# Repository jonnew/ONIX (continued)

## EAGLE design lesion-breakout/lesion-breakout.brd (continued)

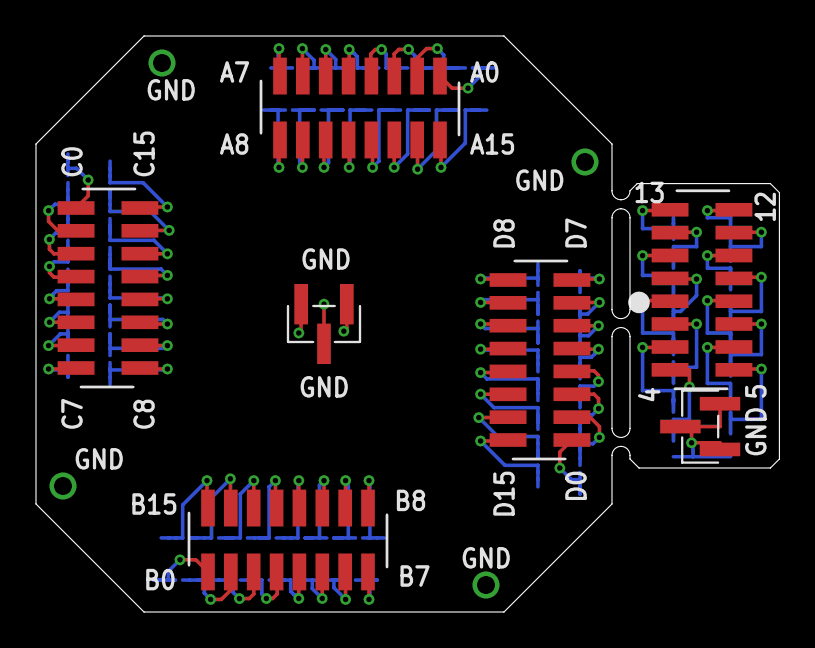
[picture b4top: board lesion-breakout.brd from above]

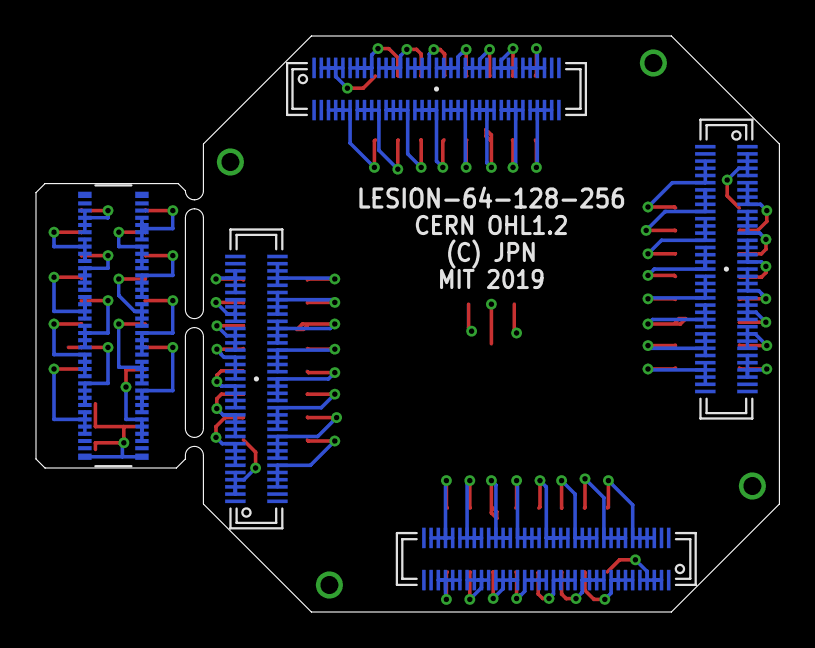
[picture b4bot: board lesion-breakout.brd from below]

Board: 2 copper layers, 41.3 x 32.0 mm, 16 parts (5 on the bottom side), 81 nets.

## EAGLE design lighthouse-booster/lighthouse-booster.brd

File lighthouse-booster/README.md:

# Lighthouse Synchronization Booster
This board is a modification for [HTC Vive Base
Stations](https://www.vive.com/us/accessory/base-station/) ("lighthouses") that
increases their range tracking range.

## Principle of Operation
HTC base stations work by producing alternating global synchronization flashes
using an IR LED array followed by laser curtain sweeps for 3D localization.
Because we use tiny photodiodes on our headstages (with about 1/10 the
effective area compared to those in the HTC headset), they are only capable of
working at ~3 meters from an unmodified base station. This issue is entirely
caused by the power of the global synchronization pulse. The synchronization
pulse must simultaneously blanket the entire room in IR light and therefore its
irradiance goes down as the square of distance from the base station.
Therefore, a very powerful LED array must be used. Conversely, because the
laser curtains are 2D sheets, their irradiance goes down linearly with distance
so they are easily received by the headstage at large distances without
modification.

This board is a drop in replacement for the standard LED array inside the HTC
Vive base station. It replaces the standard 15-LED array with an array of 120
LEDs.  Each set of 15 is controlled by a fast, low-side transistor switch. The
board draws about 700 mA DC at 12V. The pulse current (~60 us long, 2
MHz-modulated pulses operating at ~1% duty-cycle) is approximately 200A, with
5A for each LED.

## Power, Thermals, and Effective Tracking Distances
TODO

## Installation
TODO

## Gerber Files
{% include gerber_layers.md %}

## Bill of Materials
The BOM is located on [this google
sheet](https://docs.google.com/spreadsheets/d/1F-KWcdvH_63iXjZf0cgCfDiFX6XXW3qw6rlR8DZrFpQ/edit#gid=1349390549).

## License
Copyright Jonathan P. Newman 2017.

This documentation describes Open Hardware and is licensed under the
CERN OHL v.1.2.

You may redistribute and modify this documentation under the terms of the CERN
OHL v.1.2. (http://ohwr.org/cernohl). This documentation is distributed WITHOUT
ANY EXPRESS OR IMPLIED WARRANTY, INCLUDING OF MERCHANTABILITY, SATISFACTORY
QUALITY AND FITNESS FOR A PARTICULAR PURPOSE. Please see the CERN OHL v.1.2 for
applicable conditions

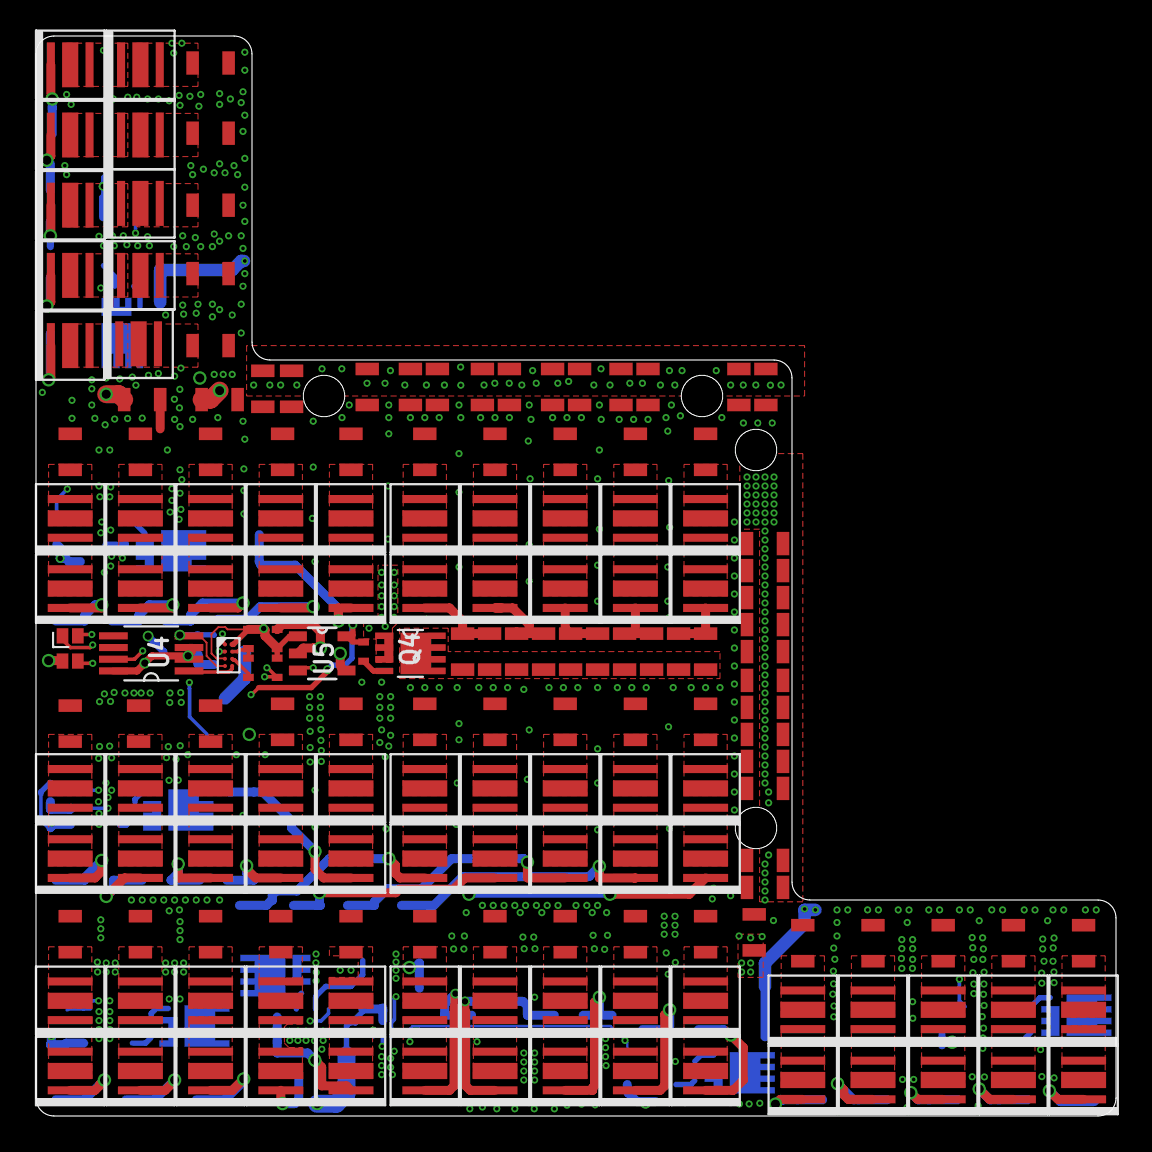
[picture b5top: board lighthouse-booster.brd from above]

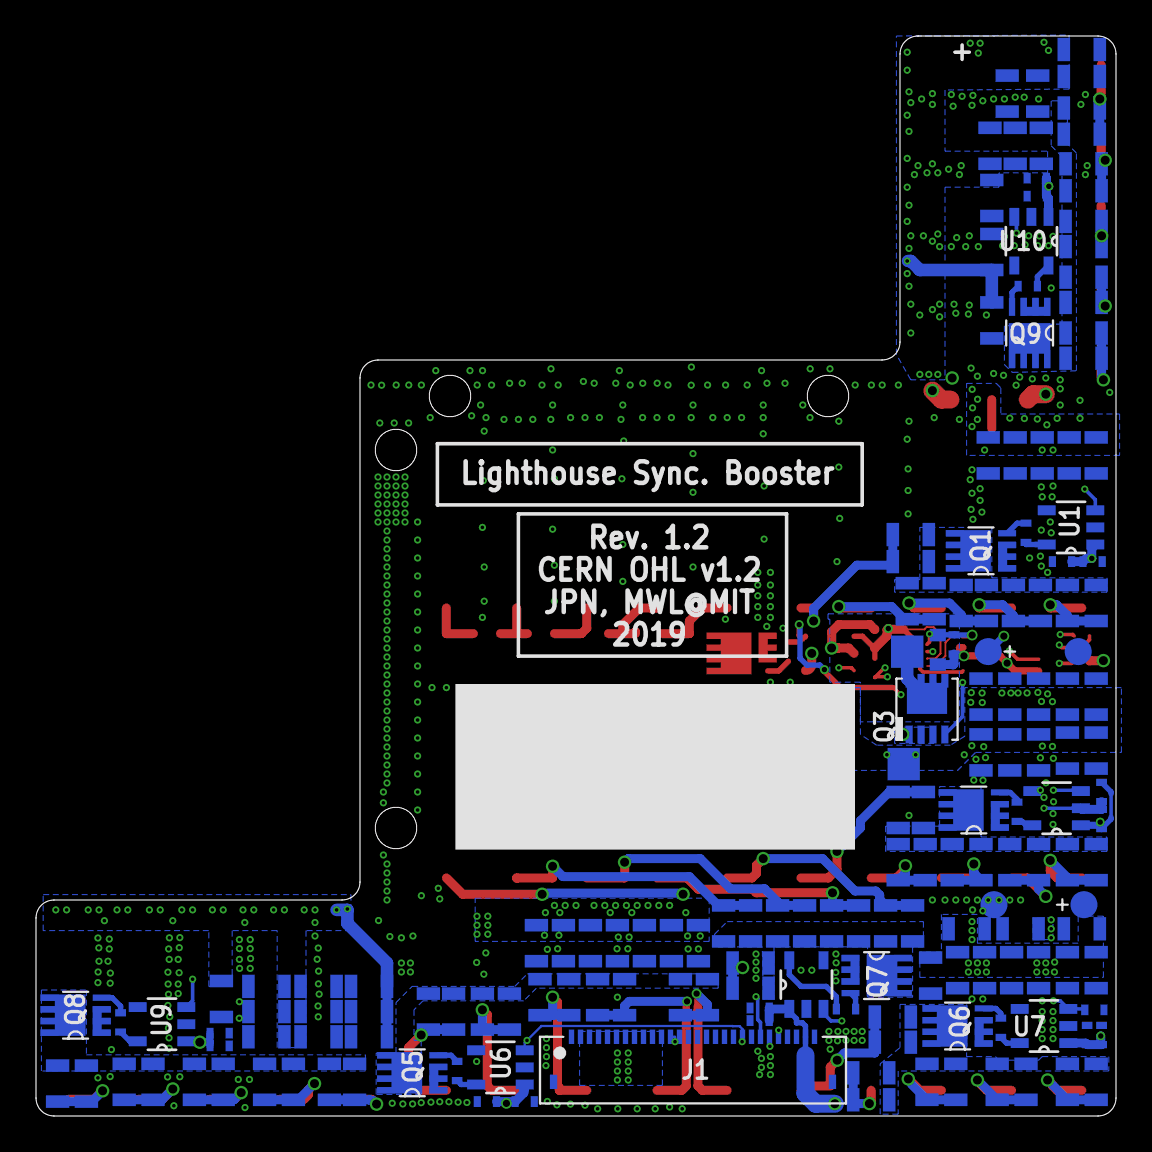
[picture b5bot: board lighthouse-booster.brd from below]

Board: 4 copper layers, 60.0 x 60.0 mm, 334 parts (166 on the bottom side), 157 nets.

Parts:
C1, C2, C6, C7, C11, C12, C13, C14, C16, C17, C18, C19, C20, C21, C22, C23, C24, C25, C26, C27, C30, C31, C32, C36, C37, C38, C42, C43, C44, C45, C46, C47, C48, C49, C50, C51, C52, C53, C54, C55, C56, C57, C58, C59, C60, C61, C62, C63, C64, C65, C66, C67, C68, C72, C73, C74, C78, C79, C80, C81, C82, C83, C84, C85, C86, C87, C88, C89, C90, C91, C92, C93, C94, C95, C96, C97, C98, C99, C100, C101: 22uF; 0805T
C3, C4, C10, C33, C34, C35, C69, C70, C71: 0.1uF; 0402T
C5: 4.7uF; 0603T
C8, C9, C39, C40, C41, C75, C76, C77: 10nF; 0402T
C15: 100pF; 0402T
C28, C29: 2.2mF; C5MMA-SMD
D2, D3, D5, D6, D8, D9, D11, D12, D14, D15, D17, D18, D20, D21, D23, D24, D26, D27, D29, D30, D33, D34, D36, D37, D39, D40, D42, D43, D45, D46, D48, D49, D51, D52, D54, D55, D57, D58, D60, D61, D63, D64, D66, D67, D69, D70, D72, D73, D75, D76, D78, D79, D81, D82, D84, D85, D87, D88, D90, D91, D93, D94, D96, D97, D99, D100, D102, D103, D105, D106, D108, D109, D111, D112, D114, D115, D117, D118, D120, D121: LUXEON-3.7MM
D31: LTST-C19HE1WT
J1: AYF532835; Y5B/Y5BW-28
L1, L2, L3, L4, L5, L6, L7, L8, L9, L10, L11, L12, L13, L14, L15, L16, L17, L18, L19, L20, L21, L22, L23, L24, L25, L26, L27, L28, L29, L30, L31, L32, L33, L34, L35, L36, L37, L38, L39, L40: 0805T
Q1, Q2, Q4, Q5, Q6, Q7, Q8, Q9: BSZ034N04LSATMA1; PG-TSDSON-8
Q3: Si7655ADN; POWERPACK-1212-8
R1, R2, R3, R4, R6, R7, R8, R9, R11, R12, R13, R14, R15, R16, R17, R18, R21, R22, R23, R24, R25, R26, R27, R28, R29, R30, R31, R32, R33, R34, R35, R36, R37, R38, R39, R40, R41, R42, R43, R44, R45, R46, R47, R48, R52, R53, R54, R55, R56, R57, R58, R59, R60, R61, R62, R63, R64, R65, R66, R67, R68, R69, R70, R71, R72, R73, R74, R75, R76, R77, R78, R79, R80, R81, R85, R86, R87, R88, R89, R90: 0.36; 0805T
R5, R10: 10k; 0402T
R19, R20, R49, R50, R51, R82, R83, R84: 10; 0402T
TP1, TP2: TP18SQ
U1, U2, U5, U6, U7, U8, U9, U10: UCC27517DBVR; SOT-23-5
U3: SN74LVC1G123YZPR; DSBGA8-1.9X0.9MM
U4: LTC1693-5; MSOP-8-3X3

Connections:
+5V0: C3.1, C4.1, C8.1, C9.1, C33.1, C34.1, C35.1, C39.1, C40.1, C41.1, C69.1, C70.1, C71.1, C75.1, C76.1, C77.1, D31.4, J1.27, R10.1, U1.1, U2.1, U3.A2, U3.C1, U5.1, U6.1, U7.1, U8.1, U9.1, U10.1
+12V: C1.2, C2.2, C6.2, C7.2, C11.2, C12.2, C13.2, C14.2, C16.2, C17.2, C18.1, C19.1, C20.1, C21.1, C22.1, C23.1, C24.1, C25.1, C26.1, C27.1, C28.A, C29.A, C30.2, C31.2, C32.2, C36.2, C37.2, C38.2, C42.2, C43.2, C44.2, C45.2, C46.2, C47.2, C48.2, C49.2, C50.2, C51.1, C52.1, C53.1, C54.1, C55.1, C56.1, C57.1, C58.1, C59.1, C60.1, C61.1, C62.1, C63.1, C64.1, C65.1, C66.2, C67.2, C68.2, C72.2, C73.2, C74.2, C78.2, C79.2, C80.2, C81.2, C82.2, C83.2, C84.2, C85.2, C86.1, C87.1, C88.1, C89.1, C90.1, C91.1, C92.1, C93.1, C94.1, C95.1, C96.1, C97.1, C98.1, C99.1, C100.1, C101.1, L1.1, L2.1, L3.1, L4.1, L5.1, L6.1, L7.1, L8.1, L9.1, L10.1, L11.1, L12.1, L13.1, L14.1, L15.1, L16.1, L17.1, L18.1, L19.1, L20.1, L21.1, L22.1, L23.1, L24.1, L25.1, L26.1, L27.1, L28.1, L29.1, L30.1, L31.1, L32.1, L33.1, L34.1, L35.1, L36.1, L37.1, L38.1, L39.1, L40.1, TP2.TP
BLUE_C: D31.3, J1.24
GND: C1.1, C2.1, C3.2, C4.2, C5.2, C6.1, C7.1, C8.2, C9.2, C10.2, C11.1, C12.1, C13.1, C14.1, C16.1, C17.1, C18.2, C19.2, C20.2, C21.2, C22.2, C23.2, C24.2, C25.2, C26.2, C27.2, C28.C, C29.C, C30.1, C31.1, C32.1, C33.2, C34.2, C35.2, C36.1, C37.1, C38.1, C39.2, C40.2, C41.2, C42.1, C43.1, C44.1, C45.1, C46.1, C47.1, C48.1, C49.1, C50.1, C51.2, C52.2, C53.2, C54.2, C55.2, C56.2, C57.2, C58.2, C59.2, C60.2, C61.2, C62.2, C63.2, C64.2, C65.2, C66.1, C67.1, C68.1, C69.2, C70.2, C71.2, C72.1, C73.1, C74.1, C75.2, C76.2, C77.2, C78.1, C79.1, C80.1, C81.1, C82.1, C83.1, C84.1, C85.1, C86.2, C87.2, C88.2, C89.2, C90.2, C91.2, C92.2, C93.2, C94.2, C95.2, C96.2, C97.2, C98.2, C99.2, C100.2, C101.2, J1.1, J1.12, J1.13, J1.14, J1.15, J1.19, J1.21, J1.25, J1.28, Q1.1, Q1.2, Q1.3, Q2.1, Q2.2, Q2.3, Q4.1, Q4.2, Q4.3, Q5.1, Q5.2, Q5.3, Q6.1, Q6.2, Q6.3, Q7.1, Q7.2, Q7.3, Q8.1, Q8.2, Q8.3, Q9.1, Q9.2, Q9.3, R5.1, U1.2, U1.4, U2.2, U2.4, U3.A1, U3.D1, U4.4, U5.2, U5.4, U6.2, U6.4, U7.2, U7.4, U8.2, U8.4, U9.2, U9.4, U10.2, U10.4
GREEN_C: D31.2, J1.23
unnamed: D76.C, R54.2, R57.2
unnamed: D75.C, D76.A1, D76.A2
unnamed: D75.A1, D75.A2, L35.2
unnamed: Q6.5, Q6.6, Q6.7, Q6.8, R27.1, R30.1, R33.1, R36.1, R39.1, R42.1, R45.1, R48.1, R54.1, R57.1
unnamed: R49.1, U7.5
unnamed: D58.C, R39.2, R42.2
unnamed: D57.C, D58.A1, D58.A2
unnamed: D67.C, R45.2, R48.2
unnamed: D66.C, D67.A1, D67.A2
unnamed: D66.A1, D66.A2, L34.2
unnamed: D30.C, R22.2, R24.2
unnamed: D57.A1, D57.A2, L33.2
unnamed: D49.C, R33.2, R36.2
unnamed: D48.C, D49.A1, D49.A2
unnamed: D48.A1, D48.A2, L32.2
unnamed: D40.C, R27.2, R30.2
unnamed: D39.C, D40.A1, D40.A2
unnamed: D39.A1, D39.A2, L31.2
unnamed: D29.C, D30.A1, D30.A2
unnamed: D29.A1, D29.A2, L20.2
unnamed: Q2.5, Q2.6, Q2.7, Q2.8, R2.1, R4.1, R7.1, R9.1, R12.1, R14.1, R16.1, R18.1, R22.1, R24.1
unnamed: R82.1, U8.5
unnamed: Q6.4, R49.2
unnamed: R50.1, U3.B1, U5.5
unnamed: Q1.4, R19.2
unnamed: R20.1, U2.5
unnamed: Q5.4, R51.2
unnamed: R83.1, U9.5
unnamed: D24.C, R16.2, R18.2
unnamed: D23.C, D24.A1, D24.A2
unnamed: D23.A1, D23.A2, L19.2
unnamed: D18.C, R12.2, R14.2
unnamed: D17.C, D18.A1, D18.A2
unnamed: D17.A1, D17.A2, L18.2
unnamed: D12.C, R7.2, R9.2
unnamed: D11.C, D12.A1, D12.A2
unnamed: D11.A1, D11.A2, L17.2
unnamed: D6.C, R2.2, R4.2
unnamed: D5.C, D6.A1, D6.A2
unnamed: D5.A1, D5.A2, L16.2
unnamed: Q2.4, R20.2
unnamed: R84.1, U10.5
unnamed: C15.1, R10.2, U3.B2
unnamed: U3.D2, U4.1
unnamed: C15.2, U3.C2
unnamed: C5.1, C10.1, J1.2, J1.3, J1.4, J1.5, J1.6, J1.7, J1.8, J1.9, J1.10, J1.11, Q3.1, Q3.2, Q3.3, U4.3, U4.8
unnamed: D27.C, R21.2, R23.2
unnamed: D26.C, D27.A1, D27.A2
unnamed: D26.A1, D26.A2, L5.2
unnamed: Q1.5, Q1.6, Q1.7, Q1.8, R1.1, R3.1, R6.1, R8.1, R11.1, R13.1, R15.1, R17.1, R21.1, R23.1
unnamed: Q3.5, Q3.6, Q3.7, Q3.8, Q3.PAD, TP1.TP
unnamed: D21.C, R15.2, R17.2
unnamed: D20.C, D21.A1, D21.A2
unnamed: D20.A1, D20.A2, L4.2
unnamed: D15.C, R11.2, R13.2
unnamed: D14.C, D15.A1, D15.A2
unnamed: D14.A1, D14.A2, L3.2
unnamed: D9.C, R6.2, R8.2
unnamed: D8.C, D9.A1, D9.A2
unnamed: D8.A1, D8.A2, L2.2
unnamed: D3.C, R1.2, R3.2
unnamed: D2.C, D3.A1, D3.A2
unnamed: D2.A1, D2.A2, L1.2
unnamed: R19.1, U1.5
unnamed: Q3.4, U4.7
unnamed: D70.C, R52.2, R55.2
unnamed: D69.C, D70.A1, D70.A2
unnamed: D69.A1, D69.A2, L10.2
unnamed: Q4.5, Q4.6, Q4.7, Q4.8, R25.1, R28.1, R31.1, R34.1, R37.1, R40.1, R43.1, R46.1, R52.1, R55.1
unnamed: D61.C, R43.2, R46.2
unnamed: D60.C, D61.A1, D61.A2
unnamed: D60.A1, D60.A2, L9.2
unnamed: D52.C, R37.2, R40.2
unnamed: D51.C, D52.A1, D52.A2
unnamed: D51.A1, D51.A2, L8.2
unnamed: D43.C, R31.2, R34.2
unnamed: D42.C, D43.A1, D43.A2
unnamed: D42.A1, D42.A2, L7.2
unnamed: D34.C, R25.2, R28.2
unnamed: D33.C, D34.A1, D34.A2
unnamed: D33.A1, D33.A2, L6.2
unnamed: Q4.4, R50.2
unnamed: D115.C, R85.2, R88.2
unnamed: D114.C, D115.A1, D115.A2
unnamed: D114.A1, D114.A2, L15.2
unnamed: Q7.5, Q7.6, Q7.7, Q7.8, R58.1, R61.1, R64.1, R67.1, R70.1, R73.1, R76.1, R79.1, R85.1, R88.1
unnamed: D106.C, R76.2, R79.2
unnamed: D105.C, D106.A1, D106.A2
unnamed: D105.A1, D105.A2, L14.2
unnamed: D97.C, R70.2, R73.2
unnamed: D96.C, D97.A1, D97.A2
unnamed: D96.A1, D96.A2, L13.2
unnamed: D88.C, R64.2, R67.2
unnamed: D87.C, D88.A1, D88.A2
unnamed: D87.A1, D87.A2, L12.2
unnamed: D79.C, R58.2, R61.2
unnamed: D78.C, D79.A1, D79.A2
unnamed: D78.A1, D78.A2, L11.2
unnamed: Q7.4, R82.2
unnamed: D73.C, R53.2, R56.2
unnamed: D72.C, D73.A1, D73.A2
unnamed: D72.A1, D72.A2, L25.2
unnamed: Q5.5, Q5.6, Q5.7, Q5.8, R26.1, R29.1, R32.1, R35.1, R38.1, R41.1, R44.1, R47.1, R53.1, R56.1
unnamed: D64.C, R44.2, R47.2
unnamed: D63.C, D64.A1, D64.A2
unnamed: D63.A1, D63.A2, L24.2
unnamed: D55.C, R38.2, R41.2
unnamed: D54.C, D55.A1, D55.A2
unnamed: D54.A1, D54.A2, L23.2
unnamed: D46.C, R32.2, R35.2
unnamed: D45.C, D46.A1, D46.A2
unnamed: D45.A1, D45.A2, L22.2
unnamed: D37.C, R26.2, R29.2
unnamed: D36.C, D37.A1, D37.A2
unnamed: D36.A1, D36.A2, L21.2
unnamed: R51.1, U6.5
unnamed: D118.C, R86.2, R89.2
unnamed: D117.C, D118.A1, D118.A2
unnamed: D117.A1, D117.A2, L30.2
unnamed: Q8.5, Q8.6, Q8.7, Q8.8, R59.1, R62.1, R65.1, R68.1, R71.1, R74.1, R77.1, R80.1, R86.1, R89.1
unnamed: D109.C, R77.2, R80.2
unnamed: D108.C, D109.A1, D109.A2
unnamed: D108.A1, D108.A2, L29.2
unnamed: D100.C, R71.2, R74.2
unnamed: D99.C, D100.A1, D100.A2
unnamed: D99.A1, D99.A2, L28.2
unnamed: D91.C, R65.2, R68.2
unnamed: D90.C, D91.A1, D91.A2
unnamed: D90.A1, D90.A2, L27.2
unnamed: D82.C, R59.2, R62.2
unnamed: D81.C, D82.A1, D82.A2
unnamed: D81.A1, D81.A2, L26.2
unnamed: Q8.4, R83.2
unnamed: D121.C, R87.2, R90.2
unnamed: D120.C, D121.A1, D121.A2
unnamed: D120.A1, D120.A2, L40.2
unnamed: Q9.5, Q9.6, Q9.7, Q9.8, R60.1, R63.1, R66.1, R69.1, R72.1, R75.1, R78.1, R81.1, R87.1, R90.1
unnamed: D112.C, R78.2, R81.2
unnamed: D111.C, D112.A1, D112.A2
unnamed: D111.A1, D111.A2, L39.2
unnamed: D103.C, R72.2, R75.2
unnamed: D102.C, D103.A1, D103.A2
unnamed: D102.A1, D102.A2, L38.2
unnamed: D94.C, R66.2, R69.2
unnamed: D93.C, D94.A1, D94.A2
unnamed: D93.A1, D93.A2, L37.2
unnamed: D85.C, R60.2, R63.2
unnamed: D84.C, D85.A1, D85.A2
unnamed: D84.A1, D84.A2, L36.2
unnamed: Q9.4, R84.2
RED_C: D31.1, J1.22
SYNC: J1.20, R5.2, U1.3, U2.3, U5.3, U6.3, U7.3, U8.3, U9.3, U10.3

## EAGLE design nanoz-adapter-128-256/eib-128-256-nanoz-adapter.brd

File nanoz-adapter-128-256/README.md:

# nanoz-adapter-128-256
Multiplexed adapter to interface eib-128 and eib-256 with the popular
[nanoZ](http://www.white-matter.com/nanoz/) electrode impedance tester and
plating device.

## Gerber Files
{% include gerber_layers.md %}

## Bill of Materials
The BOM is located on [this google
sheet](https://docs.google.com/spreadsheets/d/1F-KWcdvH_63iXjZf0cgCfDiFX6XXW3qw6rlR8DZrFpQ/edit#gid=889124438).

## Electrode Mapping
The NanoZ internal channel number to EIB mapping for [eib-128](../README.md) and [eib-256](../eib-256/README.md) are provided in the following google sheets:
- [eib-128 channel mapping](https://docs.google.com/spreadsheets/d/11wRDYOqHN5lPb03yUdfXfK0zvaDYsVetplaNK-R90Gg/edit#gid=663991061)
- [eib-256 channel mapping](https://docs.google.com/spreadsheets/d/11wRDYOqHN5lPb03yUdfXfK0zvaDYsVetplaNK-R90Gg/edit#gid=538743909)

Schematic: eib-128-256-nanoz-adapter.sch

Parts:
A: DF40HEAD; DF40-70REC
B: DF40HEAD; DF40-70REC
C: DF40HEAD; DF40-70REC
C1, C2, C5, C6, C10, C12, C13, C15, C20, C22, C23, C25, C29, C30, C33, C34: 1uF; 0603
C3, C4, C7, C8, C9, C11, C14, C16, C19, C21, C24, C26, C27, C28, C31, C32: 0.1uF; 0402
C17, C18: 10uF; 1210-POL
D: DF40HEAD; DF40-70REC
D1, D2: MMSZ5240BS; SOD-323; PARTNO UDZ10B-7
D3, D4: LED_0603; LED-0603
J1, J2, J3, J4, J5: JP3E_SMD; JP3_SMD
J6: SCREW4
J7, J8: PINHD-4X10_MOLC-THRU; MOLC-110-11-S-Q
Q1: DMN3404L; SOT23-GSD; PARTNO DMN3404L-7
Q2: DMP3056L; SOT23-GSD; PARTNO DMP3056L-7
R1, R2, R5, R6: 1k; 0603
R3, R4: 10k; 0603
S1: 219-2MSTR; SMS-002
U1, U2, U3, U4, U5, U6, U7, U8, U9, U10, U11, U12, U13, U14, U15, U16, U17, U18, U19, U20, U21, U22, U23, U24, U25, U26, U27, U28, U29, U30, U31, U32: DG4052A; MQFN16-1.8X2.6

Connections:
A: J1.2, R3.1, U1.8 (A), U2.8 (A), U3.8 (A), U4.8 (A), U5.8 (A), U6.8 (A), U7.8 (A), U8.8 (A), U9.8 (A), U10.8 (A), U11.8 (A), U12.8 (A), U13.8 (A), U14.8 (A), U15.8 (A), U16.8 (A), U17.8 (A), U18.8 (A), U19.8 (A), U20.8 (A), U21.8 (A), U22.8 (A), U23.8 (A), U24.8 (A), U25.8 (A), U26.8 (A), U27.8 (A), U28.8 (A), U29.8 (A), U30.8 (A), U31.8 (A), U32.8 (A)
B: J2.2, R4.1, U1.7 (B), U2.7 (B), U3.7 (B), U4.7 (B), U5.7 (B), U6.7 (B), U7.7 (B), U8.7 (B), U9.7 (B), U10.7 (B), U11.7 (B), U12.7 (B), U13.7 (B), U14.7 (B), U15.7 (B), U16.7 (B), U17.7 (B), U18.7 (B), U19.7 (B), U20.7 (B), U21.7 (B), U22.7 (B), U23.7 (B), U24.7 (B), U25.7 (B), U26.7 (B), U27.7 (B), U28.7 (B), U29.7 (B), U30.7 (B), U31.7 (B), U32.7 (B)
GND: C1.2, C2.2, C3.2, C4.2, C5.2, C6.2, C7.2, C8.2, C9.2, C10.2, C11.2, C12.2, C13.2, C14.2, C15.2, C16.2, C17.-, C18.+, C19.2, C20.2, C21.2, C22.2, C23.2, C24.2, C25.2, C26.2, C27.2, C28.2, C29.2, C30.2, C31.2, C32.2, C33.2, C34.2, D3.C, D4.A, J3.1, J3.2, J6.3, R1.1, R2.2, S1.1, S1.2, U1.4 (EN), U1.6 (GND), U2.4 (EN), U2.6 (GND), U3.4 (EN), U3.6 (GND), U4.4 (EN), U4.6 (GND), U5.4 (EN), U5.6 (GND), U6.4 (EN), U6.6 (GND), U7.4 (EN), U7.6 (GND), U8.4 (EN), U8.6 (GND), U9.4 (EN), U9.6 (GND), U10.4 (EN), U10.6 (GND), U11.4 (EN), U11.6 (GND), U12.4 (EN), U12.6 (GND), U14.4 (EN), U14.6 (GND), U15.4 (EN), U15.6 (GND), U16.4 (EN), U16.6 (GND), U17.4 (EN), U17.6 (GND), U18.4 (EN), U18.6 (GND), U19.4 (EN), U19.6 (GND), U20.4 (EN), U20.6 (GND), U21.4 (EN), U21.6 (GND), U22.4 (EN), U22.6 (GND), U24.4 (EN), U24.6 (GND), U25.4 (EN), U25.6 (GND), U26.4 (EN), U26.6 (GND), U27.4 (EN), U27.6 (GND), U28.4 (EN), U28.6 (GND), U29.4 (EN), U29.6 (GND), U30.4 (EN), U30.6 (GND), U32.4 (EN), U32.6 (GND)
GND1: U13.6 (GND)
GND2: U23.6 (GND)
GND4: U31.6 (GND)
GND_HEAD: J3.3, J7.B4 (17)
GPIO0_HEAD: J1.1, J7.C3 (3)
GPIO1_HEAD: J2.1, J7.C4 (4)
GPIO2_HEAD: J8.C3 (3)
GPIO3_HEAD: J8.C4 (4)
unnamed: C.2, U1.9 (X3)
unnamed: C.3, U1.10 (X0)
unnamed: C.4, U1.12 (X1)
unnamed: C.5, U1.13 (X2)
unnamed: C.6, U1.15 (Y0)
unnamed: C.7, U1.16 (Y2)
unnamed: C.8, U1.2 (Y3)
unnamed: C.9, U1.3 (Y1)
unnamed: C.10, U2.9 (X3)
unnamed: C.11, U2.10 (X0)
unnamed: C.12, U2.12 (X1)
unnamed: C.13, U2.13 (X2)
unnamed: C.14, U2.15 (Y0)
unnamed: C.15, U2.16 (Y2)
unnamed: C.16, U2.2 (Y3)
unnamed: C.17, U2.3 (Y1)
unnamed: C.18, U3.9 (X3)
unnamed: C.19, U3.10 (X0)
unnamed: C.20, U3.12 (X1)
unnamed: C.21, U3.13 (X2)
unnamed: C.22, U3.15 (Y0)
unnamed: C.23, U3.16 (Y2)
unnamed: C.24, U3.2 (Y3)
unnamed: C.25, U3.3 (Y1)
unnamed: C.26, U4.9 (X3)
unnamed: C.27, U4.10 (X0)
unnamed: C.28, U4.12 (X1)
unnamed: C.29, U4.13 (X2)
unnamed: C.30, U4.15 (Y0)
unnamed: C.31, U4.16 (Y2)
unnamed: C.32, U4.2 (Y3)
unnamed: C.33, U4.3 (Y1)
unnamed: C.41, U8.13 (X2)
unnamed: C.42, U8.12 (X1)
unnamed: C.43, U8.10 (X0)
unnamed: C.44, U8.9 (X3)
unnamed: C.45, U7.3 (Y1)
unnamed: C.46, U7.2 (Y3)
unnamed: C.47, U7.16 (Y2)
unnamed: C.48, U7.15 (Y0)
unnamed: C.49, U7.13 (X2)
unnamed: C.37, U8.3 (Y1)
unnamed: C.38, U8.2 (Y3)
unnamed: C.39, U8.16 (Y2)
unnamed: C.40, U8.15 (Y0)
unnamed: C.50, U7.12 (X1)
unnamed: C.51, U7.10 (X0)
unnamed: C.52, U7.9 (X3)
unnamed: C.53, U6.3 (Y1)
unnamed: C.54, U6.2 (Y3)
unnamed: C.55, U6.16 (Y2)
unnamed: C.56, U6.15 (Y0)
unnamed: C.57, U6.13 (X2)
unnamed: C.58, U6.12 (X1)
unnamed: C.59, U6.10 (X0)
unnamed: C.60, U6.9 (X3)
unnamed: C.61, U5.3 (Y1)
unnamed: C.62, U5.2 (Y3)
unnamed: C.63, U5.16 (Y2)
unnamed: C.64, U5.15 (Y0)
unnamed: C.65, U5.13 (X2)
unnamed: C.66, U5.12 (X1)
unnamed: C.67, U5.10 (X0)
unnamed: C.68, U5.9 (X3)
unnamed: D3.A, R5.1
unnamed: D1.A, Q2.G, R1.2
unnamed: D4.C, R6.2
unnamed: D2.C, Q1.G, R2.1
unnamed: J1.3, S1.4
unnamed: J2.3, S1.3
REF: J6.4, J7.B1 (20), J7.C1 (1), J7.C2 (2), J8.B1 (20), J8.C1 (1), J8.C2 (2)
TT00: J8.A1 (1), U24.11 (X)
TT01: J8.A2 (2), U24.1 (Y)
TT02: J8.A3 (3), U23.11 (X)
TT03: J8.A4 (4), U23.1 (Y)
TT04: J8.A5 (5), U21.11 (X)
TT05: J8.B5 (16), U21.1 (Y)
TT06: J8.A6 (6), U19.11 (X)
TT07: J8.B6 (15), U19.1 (Y)
TT08: J8.A10 (10), U11.11 (X)
TT09: J8.B10 (11), U11.1 (Y)
TT10: J8.A9 (9), U13.11 (X)
TT11: J8.B9 (12), U13.1 (Y)
TT12: J8.A8 (8), U15.11 (X)
TT13: J8.B8 (13), U15.1 (Y)
TT14: J8.A7 (7), U17.11 (X)
TT15: J8.B7 (14), U17.1 (Y)
TT16: J8.C10 (10), U1.11 (X)
TT17: J8.D10 (11), U1.1 (Y)
TT18: J8.C9 (9), U2.11 (X)
TT19: J8.D9 (12), U2.1 (Y)
TT20: J8.C8 (8), U3.11 (X)
TT21: J8.D8 (13), U3.1 (Y)
TT22: J8.C7 (7), U4.11 (X)
TT23: J8.D7 (14), U4.1 (Y)
TT24: J8.D2 (19), U8.11 (X)
TT25: J8.D1 (20), U8.1 (Y)
TT26: J8.D4 (17), U7.11 (X)
TT27: J8.D3 (18), U7.1 (Y)
TT28: J8.C5 (5), U6.11 (X)
TT29: J8.D5 (16), U6.1 (Y)
TT30: J8.C6 (6), U5.11 (X)
TT31: J8.D6 (15), U5.1 (Y)
TT32: J7.C10 (10), U9.11 (X)
TT33: J7.D10 (11), U9.1 (Y)
TT34: J7.C9 (9), U10.11 (X)
TT35: J7.D9 (12), U10.1 (Y)
TT36: J7.C8 (8), U12.11 (X)
TT37: J7.D8 (13), U12.1 (Y)
TT38: J7.C7 (7), U14.11 (X)
TT39: J7.D7 (14), U14.1 (Y)
TT40: J7.D2 (19), U22.11 (X)
TT41: J7.D1 (20), U22.1 (Y)
TT42: J7.D4 (17), U20.11 (X)
TT43: J7.D3 (18), U20.1 (Y)
TT44: J7.C5 (5), U18.11 (X)
TT45: J7.D5 (16), U18.1 (Y)
TT46: J7.C6 (6), U16.11 (X)
TT47: J7.D6 (15), U16.1 (Y)
TT48: J7.A1 (1), U32.11 (X)
TT49: J7.A2 (2), U32.1 (Y)
TT50: J7.A3 (3), U31.11 (X)
TT51: J7.A4 (4), U31.1 (Y)
TT52: J7.A5 (5), U30.11 (X)
TT53: J7.B5 (16), U30.1 (Y)
TT54: J7.A6 (6), U29.11 (X)
TT55: J7.B6 (15), U29.1 (Y)
TT56: J7.A10 (10), U25.11 (X)
TT57: J7.B10 (11), U25.1 (Y)
TT58: J7.A9 (9), U26.11 (X)
TT59: J7.B9 (12), U26.1 (Y)
TT60: J7.A8 (8), U27.11 (X)
TT61: J7.B8 (13), U27.1 (Y)
TT62: J7.A7 (7), U28.11 (X)
TT63: J7.B7 (14), U28.1 (Y)
VCC: C1.1, C2.1, C3.1, C4.1, C9.1, C10.1, C15.1, C16.1, C17.+, C19.1, C20.1, C25.1, C26.1, C31.1, C32.1, C33.1, C34.1, D1.C, Q2.S, R3.2, R4.2, R5.2, U1.14 (V+), U2.14 (V+), U3.14 (V+), U4.14 (V+), U5.14 (V+), U6.14 (V+), U7.14 (V+), U8.14 (V+), U9.14 (V+), U10.14 (V+), U11.14 (V+), U12.14 (V+), U13.14 (V+), U14.14 (V+), U15.14 (V+), U16.14 (V+), U17.14 (V+), U18.14 (V+), U19.14 (V+), U20.14 (V+), U21.14 (V+), U22.14 (V+), U23.14 (V+), U24.14 (V+), U25.14 (V+), U26.14 (V+), U27.14 (V+), U28.14 (V+), U29.14 (V+), U30.14 (V+), U31.14 (V+), U32.14 (V+)
VCC_HEAD: J5.3, J7.B2 (19)
VCC_LOCAL: J5.1, J6.1
VCC_PRE: J5.2, Q2.D
VSS: C5.1, C6.1, C7.1, C8.1, C11.1, C12.1, C13.1, C14.1, C18.-, C21.1, C22.1, C23.1, C24.1, C27.1, C28.1, C29.1, C30.1, D2.A, Q1.S, R6.1, U1.5 (V-), U2.5 (V-), U3.5 (V-), U4.5 (V-), U5.5 (V-), U6.5 (V-), U7.5 (V-), U8.5 (V-), U9.5 (V-), U10.5 (V-), U11.5 (V-), U12.5 (V-), U13.5 (V-), U14.5 (V-), U15.5 (V-), U16.5 (V-), U17.5 (V-), U18.5 (V-), U19.5 (V-), U20.5 (V-), U21.5 (V-), U22.5 (V-), U23.5 (V-), U24.5 (V-), U25.5 (V-), U26.5 (V-), U27.5 (V-), U28.5 (V-), U29.5 (V-), U30.5 (V-), U31.5 (V-), U32.5 (V-)
VSS_HEAD: J4.3, J7.B3 (18)
VSS_LOCAL: J4.1, J6.2
VSS_PRE: J4.2, Q1.D

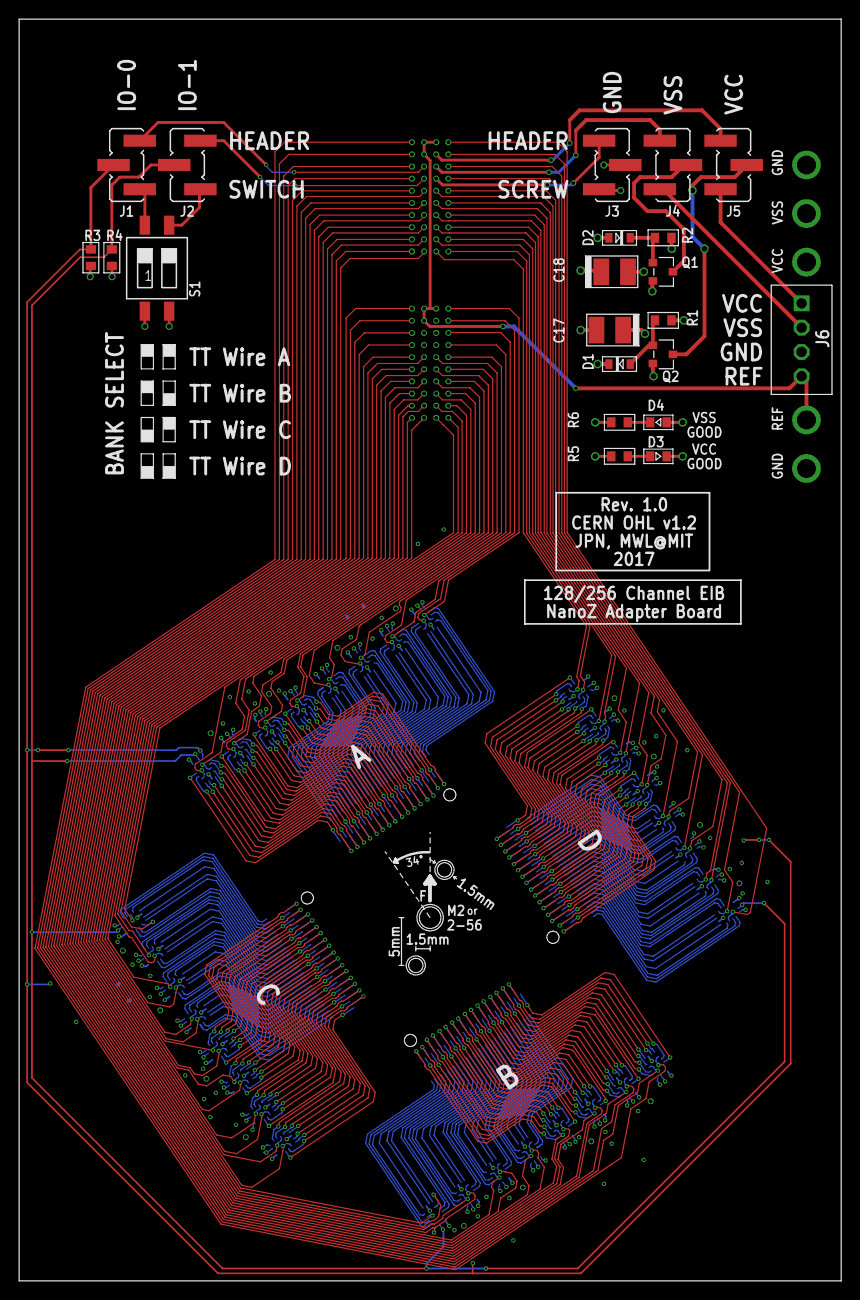
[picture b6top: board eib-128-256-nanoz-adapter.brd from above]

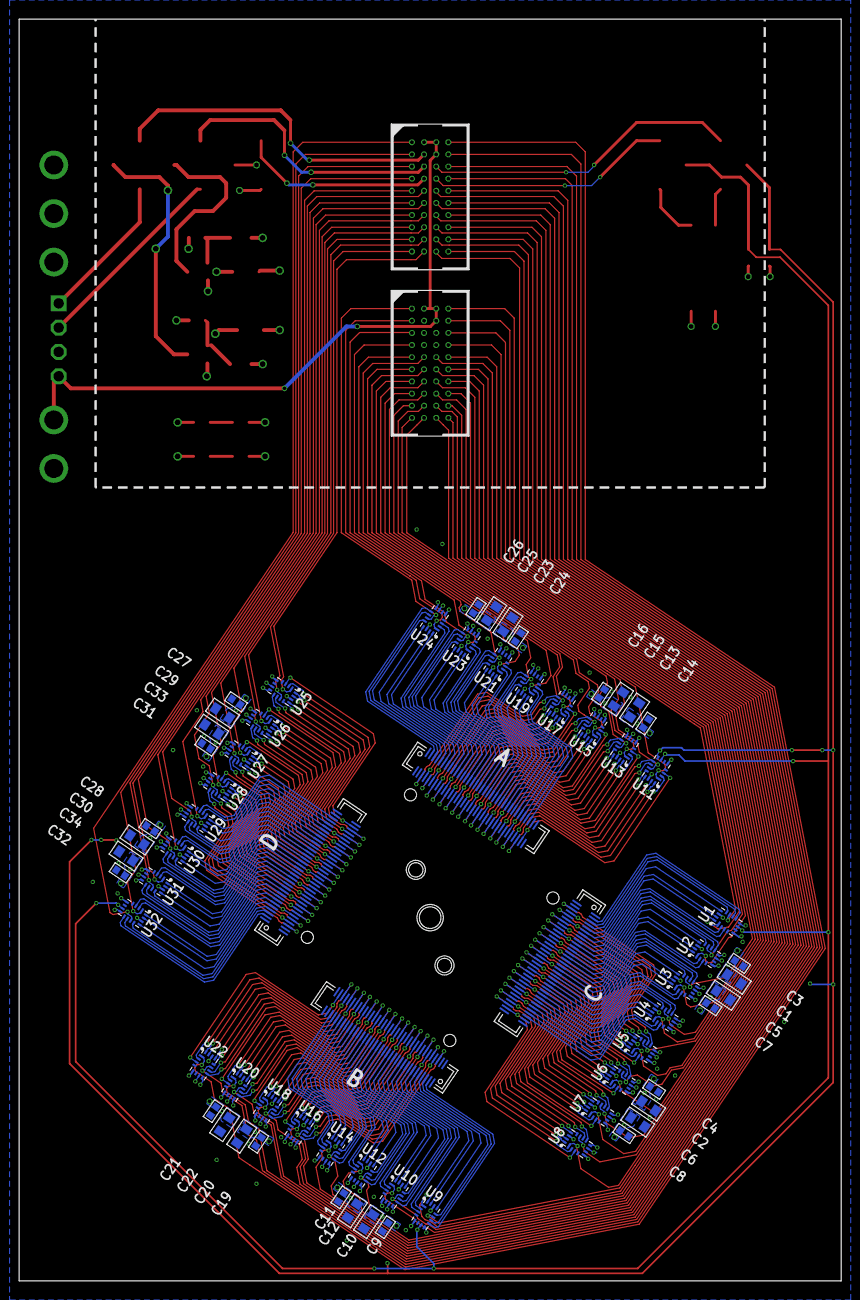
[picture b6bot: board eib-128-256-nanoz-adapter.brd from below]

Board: 4 copper layers, 86.0 x 132.0 mm, 92 parts (70 on the bottom side), 149 nets.

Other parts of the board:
U$1: EIB_MOUNT_A

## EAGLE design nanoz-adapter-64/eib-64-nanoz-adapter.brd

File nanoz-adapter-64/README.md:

# nanoz-adapter-64
Adapter to interface eib-64 with the popular
[nanoZ](http://www.white-matter.com/nanoz/) electrode impedance tester and
plating device.

## Gerber Files
{% include gerber_layers.md %}

## Bill of Materials
The BOM is located on [this google
sheet](https://docs.google.com/spreadsheets/d/1F-KWcdvH_63iXjZf0cgCfDiFX6XXW3qw6rlR8DZrFpQ/edit#gid=889124438).

## Electrode Mapping
The NanoZ internal channel number to [eib-64](../eib-64/README.md) channel mapping is provided on [this google sheet](https://docs.google.com/spreadsheets/d/11wRDYOqHN5lPb03yUdfXfK0zvaDYsVetplaNK-R90Gg/edit#gid=0).

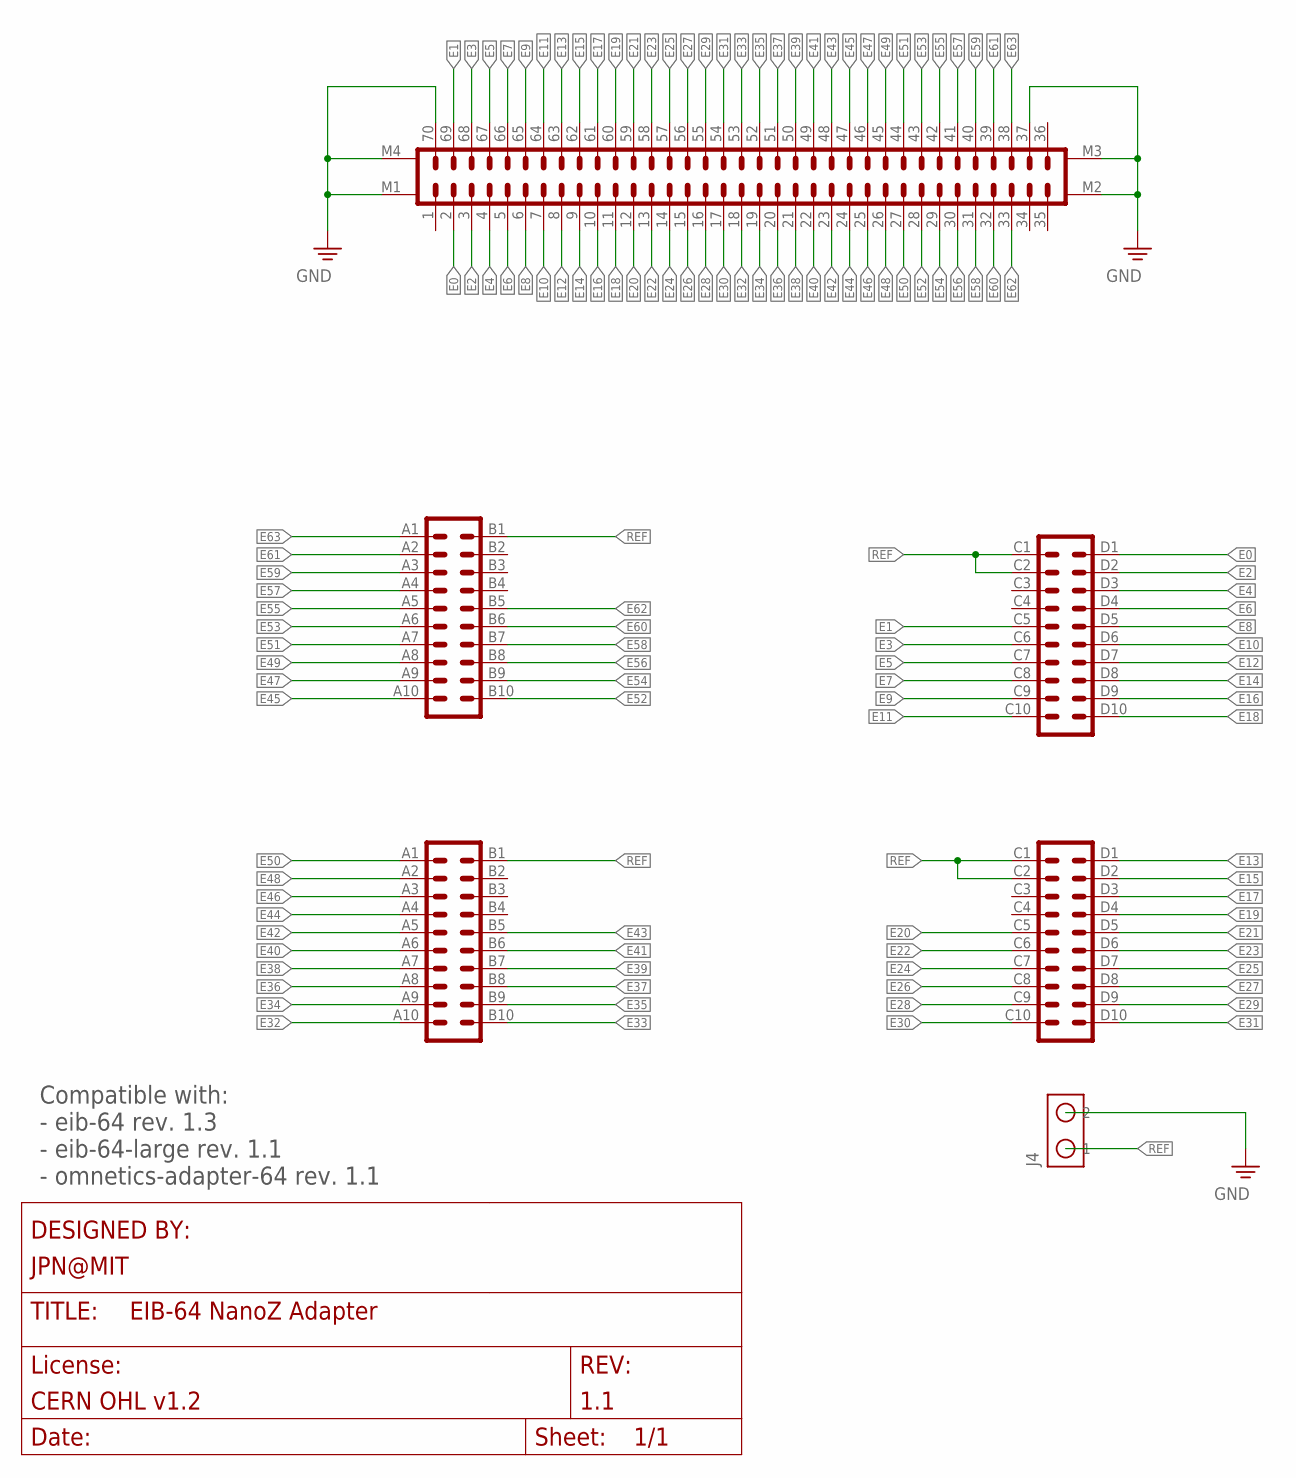
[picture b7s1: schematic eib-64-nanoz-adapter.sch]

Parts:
J1: DF40-REC; DF40-70HEAD
J2, J3: PINHD-4X10_MOLC-THRU; MOLC-110-11-S-Q
J4: SCREW2

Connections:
E0: J1.2, J2.D1 (20)
E1: J1.69, J2.C5 (5)
E2: J1.3, J2.D2 (19)
E3: J1.68, J2.C6 (6)
E4: J1.4, J2.D3 (18)
E5: J1.67, J2.C7 (7)
E6: J1.5, J2.D4 (17)
E7: J1.66, J2.C8 (8)
E8: J1.6, J2.D5 (16)
E9: J1.65, J2.C9 (9)
E10: J1.7, J2.D6 (15)
E11: J1.64, J2.C10 (10)
E12: J1.8, J2.D7 (14)
E13: J1.63, J3.D1 (20)
E14: J1.9, J2.D8 (13)
E15: J1.62, J3.D2 (19)
E16: J1.10, J2.D9 (12)
E17: J1.61, J3.D3 (18)
E18: J1.11, J2.D10 (11)
E19: J1.60, J3.D4 (17)
E20: J1.12, J3.C5 (5)
E21: J1.59, J3.D5 (16)
E22: J1.13, J3.C6 (6)
E23: J1.58, J3.D6 (15)
E24: J1.14, J3.C7 (7)
E25: J1.57, J3.D7 (14)
E26: J1.15, J3.C8 (8)
E27: J1.56, J3.D8 (13)
E28: J1.16, J3.C9 (9)
E29: J1.55, J3.D9 (12)
E30: J1.17, J3.C10 (10)
E31: J1.54, J3.D10 (11)
E32: J1.18, J3.A10 (10)
E33: J1.53, J3.B10 (11)
E34: J1.19, J3.A9 (9)
E35: J1.52, J3.B9 (12)
E36: J1.20, J3.A8 (8)
E37: J1.51, J3.B8 (13)
E38: J1.21, J3.A7 (7)
E39: J1.50, J3.B7 (14)
E40: J1.22, J3.A6 (6)
E41: J1.49, J3.B6 (15)
E42: J1.23, J3.A5 (5)
E43: J1.48, J3.B5 (16)
E44: J1.24, J3.A4 (4)
E45: J1.47, J2.A10 (10)
E46: J1.25, J3.A3 (3)
E47: J1.46, J2.A9 (9)
E48: J1.26, J3.A2 (2)
E49: J1.45, J2.A8 (8)
E50: J1.27, J3.A1 (1)
E51: J1.44, J2.A7 (7)
E52: J1.28, J2.B10 (11)
E53: J1.43, J2.A6 (6)
E54: J1.29, J2.B9 (12)
E55: J1.42, J2.A5 (5)
E56: J1.30, J2.B8 (13)
E57: J1.41, J2.A4 (4)
E58: J1.31, J2.B7 (14)
E59: J1.40, J2.A3 (3)
E60: J1.32, J2.B6 (15)
E61: J1.39, J2.A2 (2)
E62: J1.33, J2.B5 (16)
E63: J1.38, J2.A1 (1)
GND: J1.37, J1.70, J1.M1, J1.M2, J1.M3, J1.M4, J4.P$2 (2)
REF: J2.B1 (20), J2.C1 (1), J2.C2 (2), J3.B1 (20), J3.C1 (1), J3.C2 (2), J4.P$1 (1)

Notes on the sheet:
Compatible with: - eib-64 rev. 1.3 - eib-64-large rev. 1.1 - omnetics-adapter-64 rev. 1.1

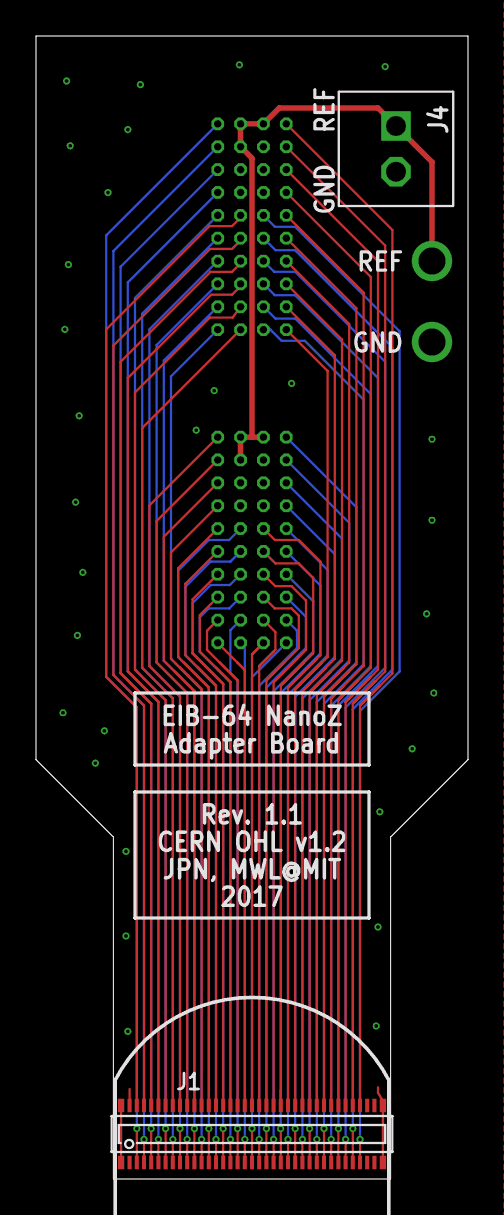
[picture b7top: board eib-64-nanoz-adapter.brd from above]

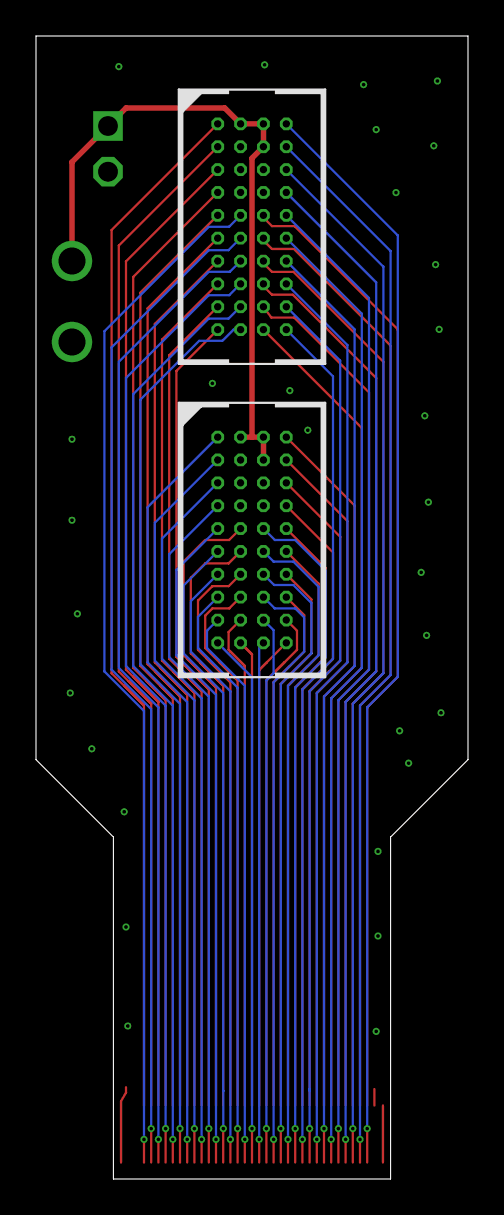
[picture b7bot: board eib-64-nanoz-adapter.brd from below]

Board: 4 copper layers, 24.0 x 63.5 mm, 4 parts (2 on the bottom side), 66 nets.
